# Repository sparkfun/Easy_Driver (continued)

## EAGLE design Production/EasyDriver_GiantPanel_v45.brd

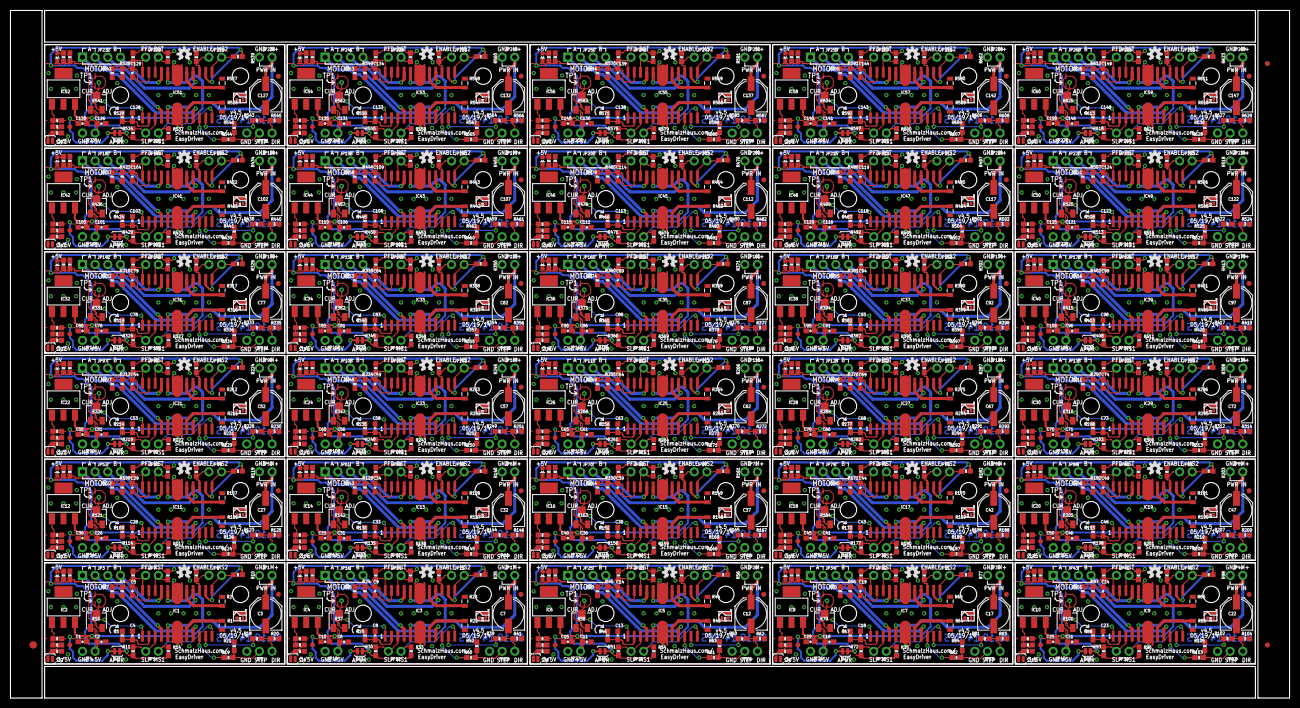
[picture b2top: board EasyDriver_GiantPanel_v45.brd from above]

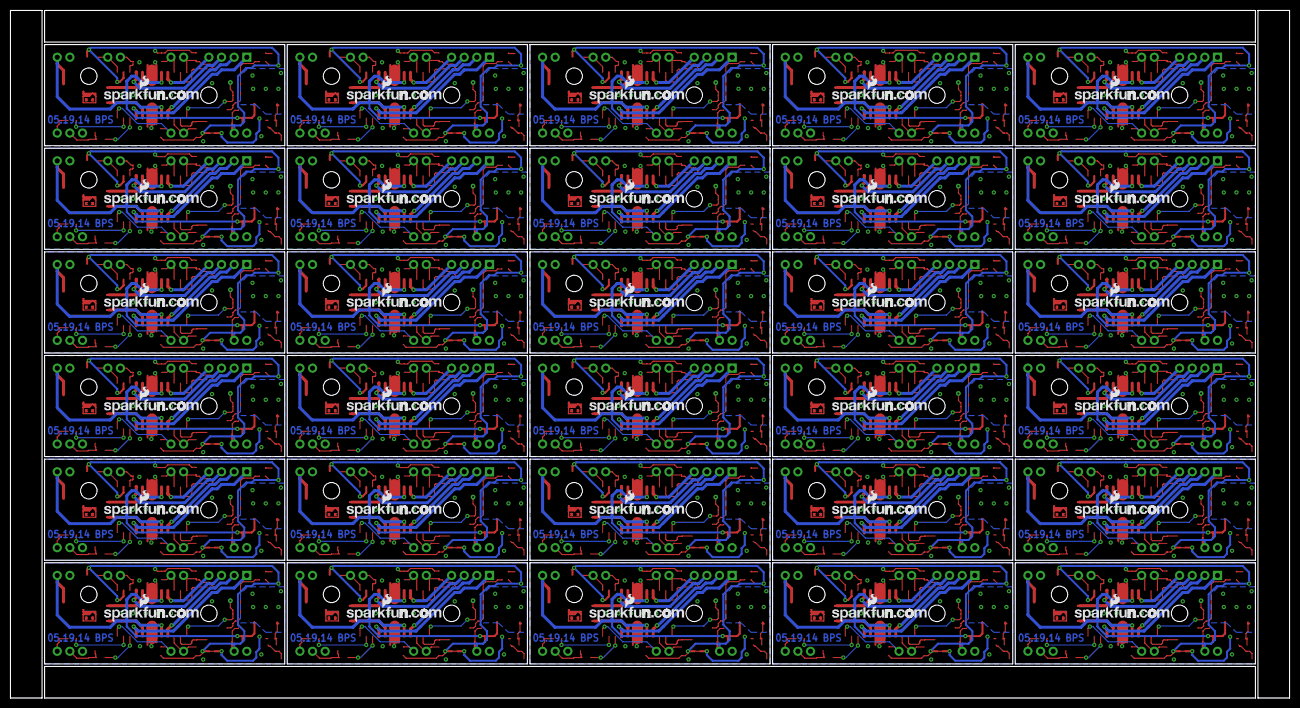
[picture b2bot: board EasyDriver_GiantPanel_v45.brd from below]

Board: 2 copper layers, 257.0 x 138.2 mm, 1383 parts (30 on the bottom side), 810 nets.

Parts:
C1, C10, C15, C20, C25, C30, C35, C40, C45, C50, C55, C60, C65, C70, C75, C80, C85, C90, C95, C100, C105, C110, C115, C120, C125, C130, C135, C140, C145, C150: .1uF; 0603-CAP
C2, C6, C11, C16, C21, C26, C31, C36, C41, C46, C51, C56, C61, C66, C71, C76, C81, C86, C91, C96, C101, C106, C111, C116, C121, C126, C131, C136, C141, C146: 1uf; 0603-CAP
C3, C7, C12, C17, C22, C27, C32, C37, C42, C47, C52, C57, C62, C67, C72, C77, C82, C87, C92, C97, C102, C107, C112, C117, C122, C127, C132, C137, C142, C147: 47uF; PANASONIC_D
C4, C5, C8, C9, C13, C14, C18, C19, C23, C24, C28, C29, C33, C34, C38, C39, C43, C44, C48, C49, C53, C54, C58, C59, C63, C64, C68, C69, C73, C74, C78, C79, C83, C84, C88, C89, C93, C94, C98, C99, C103, C104, C108, C109, C113, C114, C118, C119, C123, C124, C128, C129, C133, C134, C138, C139, C143, C144, C148, C149: 680pF; 0603-CAP
E$1: FIDUCIAL-1.5X3
E$4, E$6: FIDUCIAL-1X2
FID1, FID2, FID3, FID4, FID5, FID6, FID7, FID8, FID9, FID10, FID11, FID12, FID13, FID14, FID15, FID16, FID17, FID18, FID19, FID20, FID21, FID22, FID23, FID24, FID25, FID26, FID27, FID28, FID29, FID30, FID31, FID32, FID33, FID34, FID35, FID36, FID37, FID38, FID39, FID40, FID41, FID42, FID43, FID44, FID45, FID46, FID47, FID48, FID49, FID50, FID51, FID52, FID53, FID54, FID55, FID56, FID57, FID58, FID59, FID60: FIDUCIAL1X2; FIDUCIAL-1X2
IC1, IC3, IC5, IC7, IC9, IC11, IC13, IC15, IC17, IC19, IC21, IC23, IC25, IC27, IC29, IC31, IC33, IC35, IC37, IC39, IC41, IC43, IC45, IC47, IC49, IC51, IC53, IC55, IC57, IC59: A3967SLB; SO24W
IC2, IC4, IC6, IC8, IC10, IC12, IC14, IC16, IC18, IC20, IC22, IC24, IC26, IC28, IC30, IC32, IC34, IC36, IC38, IC40, IC42, IC44, IC46, IC48, IC50, IC52, IC54, IC56, IC58, IC60: V_REG_317SMD; SOT223
JP1, JP4, JP5, JP6, JP7, JP12, JP13, JP14, JP17, JP18, JP21, JP22, JP23, JP26, JP27, JP30, JP31, JP32, JP35, JP36, JP39, JP40, JP41, JP44, JP45, JP48, JP49, JP50, JP53, JP54, JP57, JP58, JP59, JP62, JP63, JP66, JP67, JP68, JP71, JP72, JP75, JP76, JP77, JP80, JP81, JP84, JP85, JP86, JP89, JP90, JP93, JP94, JP95, JP98, JP99, JP102, JP103, JP104, JP107, JP108, JP111, JP112, JP113, JP116, JP117, JP120, JP121, JP122, JP125, JP126, JP129, JP130, JP131, JP134, JP135, JP138, JP139, JP140, JP143, JP144, JP147, JP148, JP149, JP152, JP153, JP156, JP157, JP158, JP161, JP162, JP165, JP166, JP167, JP170, JP171, JP174, JP175, JP176, JP179, JP180, JP183, JP184, JP185, JP188, JP189, JP192, JP193, JP194, JP197, JP198, JP201, JP202, JP203, JP206, JP207, JP210, JP211, JP212, JP215, JP216, JP219, JP220, JP221, JP224, JP225, JP228, JP229, JP230, JP233, JP234, JP237, JP238, JP239, JP242, JP243, JP246, JP247, JP248, JP251, JP252, JP255, JP256, JP257, JP260, JP261, JP264, JP265, JP266, JP269, JP270: 1X02_NO_SILK
JP2, JP15, JP24, JP33, JP42, JP51, JP60, JP69, JP78, JP87, JP96, JP105, JP114, JP123, JP132, JP141, JP150, JP159, JP168, JP177, JP186, JP195, JP204, JP213, JP222, JP231, JP240, JP249, JP258, JP267: 1X03_NO_SILK
JP3, JP16, JP25, JP34, JP43, JP52, JP61, JP70, JP79, JP88, JP97, JP106, JP115, JP124, JP133, JP142, JP151, JP160, JP169, JP178, JP187, JP196, JP205, JP214, JP223, JP232, JP241, JP250, JP259, JP268: 1X04_NO_SILK
JP8, JP9, JP10, JP11, JP19, JP20, JP28, JP29, JP37, JP38, JP46, JP47, JP55, JP56, JP64, JP65, JP73, JP74, JP82, JP83, JP91, JP92, JP100, JP101, JP109, JP110, JP118, JP119, JP127, JP128, JP136, JP137, JP145, JP146, JP154, JP155, JP163, JP164, JP172, JP173, JP181, JP182, JP190, JP191, JP199, JP200, JP208, JP209, JP217, JP218, JP226, JP227, JP235, JP236, JP244, JP245, JP253, JP254, JP262, JP263: STAND-OFF
LOGO1, LOGO2, LOGO3, LOGO4, LOGO5, LOGO6, LOGO7, LOGO8, LOGO9, LOGO10, LOGO11, LOGO12, LOGO13, LOGO14, LOGO15, LOGO16, LOGO17, LOGO18, LOGO19, LOGO20, LOGO21, LOGO22, LOGO23, LOGO24, LOGO25, LOGO26, LOGO27, LOGO28, LOGO29, LOGO30: OSHW-LOGOS; OSHW-LOGO-S
PWR_LED, PWR_LED1, PWR_LED2, PWR_LED3, PWR_LED4, PWR_LED5, PWR_LED6, PWR_LED7, PWR_LED8, PWR_LED9, PWR_LED10, PWR_LED11, PWR_LED12, PWR_LED13, PWR_LED14, PWR_LED15, PWR_LED16, PWR_LED17, PWR_LED18, PWR_LED19, PWR_LED20, PWR_LED21, PWR_LED22, PWR_LED23, PWR_LED24, PWR_LED25, PWR_LED26, PWR_LED27, PWR_LED28, PWR_LED29: YELLOW; LED-0603
R1, R2, R22, R23, R43, R44, R64, R65, R85, R86, R106, R107, R127, R128, R148, R149, R169, R170, R190, R191, R211, R212, R232, R233, R253, R254, R274, R275, R295, R296, R316, R317, R337, R338, R358, R359, R379, R380, R400, R401, R421, R422, R442, R443, R463, R464, R484, R485, R505, R506, R526, R527, R547, R548, R568, R569, R589, R590, R610, R611: .75; 0805
R3, R4, R24, R25, R45, R46, R66, R67, R87, R88, R108, R109, R129, R130, R150, R151, R171, R172, R192, R193, R213, R214, R234, R235, R255, R256, R276, R277, R297, R298, R318, R319, R339, R340, R360, R361, R381, R382, R402, R403, R423, R424, R444, R445, R465, R466, R486, R487, R507, R508, R528, R529, R549, R550, R570, R571, R591, R592, R612, R613: 20K; 0603-RES
R5, R26, R47, R68, R89, R110, R131, R152, R173, R194, R215, R236, R257, R278, R299, R320, R341, R362, R383, R404, R425, R446, R467, R488, R509, R530, R551, R572, R593, R614: 2.49K; 0603-RES
R6, R27, R48, R69, R90, R111, R132, R153, R174, R195, R216, R237, R258, R279, R300, R321, R342, R363, R384, R405, R426, R447, R468, R489, R510, R531, R552, R573, R594, R615: 390; 0603-RES
R7, R36, R57, R78, R99, R120, R141, R162, R183, R204, R225, R246, R267, R288, R309, R330, R351, R372, R393, R414, R435, R456, R477, R498, R519, R540, R561, R582, R603, R624: 330; 0603-RES
R8, R28, R49, R70, R91, R112, R133, R154, R175, R196, R217, R238, R259, R280, R301, R322, R343, R364, R385, R406, R427, R448, R469, R490, R511, R532, R553, R574, R595, R616: 240; 0603-RES
R9, R18, R19, R29, R39, R40, R50, R60, R61, R71, R81, R82, R92, R102, R103, R113, R123, R124, R134, R144, R145, R155, R165, R166, R176, R186, R187, R197, R207, R208, R218, R228, R229, R239, R249, R250, R260, R270, R271, R281, R291, R292, R302, R312, R313, R323, R333, R334, R344, R354, R355, R365, R375, R376, R386, R396, R397, R407, R417, R418, R428, R438, R439, R449, R459, R460, R470, R480, R481, R491, R501, R502, R512, R522, R523, R533, R543, R544, R554, R564, R565, R575, R585, R586, R596, R606, R607, R617, R627, R628: 1K; 0603-RES
R10, R11, R12, R13, R14, R15, R20, R21, R30, R31, R32, R33, R34, R35, R41, R42, R51, R52, R53, R54, R55, R56, R62, R63, R72, R73, R74, R75, R76, R77, R83, R84, R93, R94, R95, R96, R97, R98, R104, R105, R114, R115, R116, R117, R118, R119, R125, R126, R135, R136, R137, R138, R139, R140, R146, R147, R156, R157, R158, R159, R160, R161, R167, R168, R177, R178, R179, R180, R181, R182, R188, R189, R198, R199, R200, R201, R202, R203, R209, R210, R219, R220, R221, R222, R223, R224, R230, R231, R240, R241, R242, R243, R244, R245, R251, R252, R261, R262, R263, R264, R265, R266, R272, R273, R282, R283, R284, R285, R286, R287, R293, R294, R303, R304, R305, R306, R307, R308, R314, R315, R324, R325, R326, R327, R328, R329, R335, R336, R345, R346, R347, R348, R349, R350, R356, R357, R366, R367, R368, R369, R370, R371, R377, R378, R387, R388, R389, R390, R391, R392, R398, R399, R408, R409, R410, R411, R412, R413, R419, R420, R429, R430, R431, R432, R433, R434, R440, R441, R450, R451, R452, R453, R454, R455, R461, R462, R471, R472, R473, R474, R475, R476, R482, R483, R492, R493, R494, R495, R496, R497, R503, R504, R513, R514, R515, R516, R517, R518, R524, R525, R534, R535, R536, R537, R538, R539, R545, R546, R555, R556, R557, R558, R559, R560, R566, R567, R576, R577, R578, R579, R580, R581, R587, R588, R597, R598, R599, R600, R601, R602, R608, R609, R618, R619, R620, R621, R622, R623, R629, R630: 10K; 0603-RES
R16, R37, R58, R79, R100, R121, R142, R163, R184, R205, R226, R247, R268, R289, R310, R331, R352, R373, R394, R415, R436, R457, R478, R499, R520, R541, R562, R583, R604, R625: 10K; TRIMPOT-3MM-2
R17, R38, R59, R80, R101, R122, R143, R164, R185, R206, R227, R248, R269, R290, R311, R332, R353, R374, R395, R416, R437, R458, R479, R500, R521, R542, R563, R584, R605, R626: 6.8K; 0603-RES
SJ1, SJ3, SJ5, SJ7, SJ9, SJ11, SJ13, SJ15, SJ17, SJ19, SJ21, SJ23, SJ25, SJ27, SJ29, SJ31, SJ33, SJ35, SJ37, SJ39, SJ41, SJ43, SJ45, SJ47, SJ49, SJ51, SJ53, SJ55, SJ57, SJ59: SOLDERJUMPERTRACE; SJ_2S-TRACE
SJ2, SJ4, SJ6, SJ8, SJ10, SJ12, SJ14, SJ16, SJ18, SJ20, SJ22, SJ24, SJ26, SJ28, SJ30, SJ32, SJ34, SJ36, SJ38, SJ40, SJ42, SJ44, SJ46, SJ48, SJ50, SJ52, SJ54, SJ56, SJ58, SJ60: SOLDERJUMPERNO; SJ_2S-NO
TP1, TP2, TP3, TP4, TP5, TP6, TP7, TP8, TP9, TP10, TP11, TP12, TP13, TP14, TP15, TP16, TP17, TP18, TP19, TP20, TP21, TP22, TP23, TP24, TP25, TP26, TP27, TP28, TP29, TP30: TEST-POINTTP_15TH_THRU; TP_15TH
U$1, U$3, U$5, U$7, U$9, U$11, U$13, U$15, U$17, U$19, U$21, U$23, U$25, U$27, U$29, U$31, U$33, U$35, U$37, U$39, U$41, U$43, U$45, U$47, U$49, U$51, U$53, U$55, U$57, U$59: SCHMALZHAUS_SMALL
U$2, U$4, U$6, U$8, U$10, U$12, U$14, U$16, U$18, U$20, U$22, U$24, U$26, U$28, U$30, U$32, U$34, U$36, U$38, U$40, U$42, U$44, U$46, U$48, U$50, U$52, U$54, U$56, U$58, U$60: LOGO-SFENEW; SFE-NEW-WEBLOGO

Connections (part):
5V_ALT: IC2.2, IC2.4, R8.2, SJ1.1
5V_ALT1: IC4.2, IC4.4, R28.2, SJ3.1
5V_ALT2: IC6.2, IC6.4, R49.2, SJ5.1
5V_ALT3: IC8.2, IC8.4, R70.2, SJ7.1
5V_ALT4: IC10.2, IC10.4, R91.2, SJ9.1
5V_ALT5: IC12.2, IC12.4, R112.2, SJ11.1
5V_ALT6: IC14.2, IC14.4, R133.2, SJ13.1
5V_ALT7: IC16.2, IC16.4, R154.2, SJ15.1
5V_ALT8: IC18.2, IC18.4, R175.2, SJ17.1
5V_ALT9: IC20.2, IC20.4, R196.2, SJ19.1
5V_ALT10: IC22.2, IC22.4, R217.2, SJ21.1
5V_ALT11: IC24.2, IC24.4, R238.2, SJ23.1
5V_ALT12: IC26.2, IC26.4, R259.2, SJ25.1
5V_ALT13: IC28.2, IC28.4, R280.2, SJ27.1
5V_ALT14: IC30.2, IC30.4, R301.2, SJ29.1
5V_ALT15: IC32.2, IC32.4, R322.2, SJ31.1
5V_ALT16: IC34.2, IC34.4, R343.2, SJ33.1
5V_ALT17: IC36.2, IC36.4, R364.2, SJ35.1
5V_ALT18: IC38.2, IC38.4, R385.2, SJ37.1
5V_ALT19: IC40.2, IC40.4, R406.2, SJ39.1
5V_ALT20: IC42.2, IC42.4, R427.2, SJ41.1
5V_ALT21: IC44.2, IC44.4, R448.2, SJ43.1
5V_ALT22: IC46.2, IC46.4, R469.2, SJ45.1
5V_ALT23: IC48.2, IC48.4, R490.2, SJ47.1
5V_ALT24: IC50.2, IC50.4, R511.2, SJ49.1
5V_ALT25: IC52.2, IC52.4, R532.2, SJ51.1
5V_ALT26: IC54.2, IC54.4, R553.2, SJ53.1
5V_ALT27: IC56.2, IC56.4, R574.2, SJ55.1
5V_ALT28: IC58.2, IC58.4, R595.2, SJ57.1
5V_ALT29: IC60.2, IC60.4, R616.2, SJ59.1
DIR: IC1.11, R18.1
DIR1: IC3.11, R39.1
DIR2: IC5.11, R60.1
DIR3: IC7.11, R81.1
DIR4: IC9.11, R102.1
DIR5: IC11.11, R123.1
DIR6: IC13.11, R144.1
DIR7: IC15.11, R165.1
DIR8: IC17.11, R186.1
DIR9: IC19.11, R207.1
DIR10: IC21.11, R228.1
DIR11: IC23.11, R249.1
DIR12: IC25.11, R270.1
DIR13: IC27.11, R291.1
DIR14: IC29.11, R312.1
DIR15: IC31.11, R333.1
DIR16: IC33.11, R354.1
DIR17: IC35.11, R375.1
DIR18: IC37.11, R396.1
DIR19: IC39.11, R417.1
DIR20: IC41.11, R438.1
DIR21: IC43.11, R459.1
DIR22: IC45.11, R480.1
DIR23: IC47.11, R501.1
DIR24: IC49.11, R522.1
DIR25: IC51.11, R543.1
DIR26: IC53.11, R564.1
DIR27: IC55.11, R585.1
DIR28: IC57.11, R606.1
DIR29: IC59.11, R627.1
DIR_IN: JP2.3, R18.2, R20.2
DIR_IN1: JP15.3, R39.2, R41.2
DIR_IN2: JP24.3, R60.2, R62.2
DIR_IN3: JP33.3, R81.2, R83.2
DIR_IN4: JP42.3, R102.2, R104.2
DIR_IN5: JP51.3, R123.2, R125.2
DIR_IN6: JP60.3, R144.2, R146.2
DIR_IN7: JP69.3, R165.2, R167.2
DIR_IN8: JP78.3, R186.2, R188.2
DIR_IN9: JP87.3, R207.2, R209.2
DIR_IN10: JP96.3, R228.2, R230.2
DIR_IN11: JP105.3, R249.2, R251.2
DIR_IN12: JP114.3, R270.2, R272.2
DIR_IN13: JP123.3, R291.2, R293.2
DIR_IN14: JP132.3, R312.2, R314.2
DIR_IN15: JP141.3, R333.2, R335.2
DIR_IN16: JP150.3, R354.2, R356.2
DIR_IN17: JP159.3, R375.2, R377.2
DIR_IN18: JP168.3, R396.2, R398.2
DIR_IN19: JP177.3, R417.2, R419.2
DIR_IN20: JP186.3, R438.2, R440.2
DIR_IN21: JP195.3, R459.2, R461.2
DIR_IN22: JP204.3, R480.2, R482.2
DIR_IN23: JP213.3, R501.2, R503.2
DIR_IN24: JP222.3, R522.2, R524.2
DIR_IN25: JP231.3, R543.2, R545.2
DIR_IN26: JP240.3, R564.2, R566.2
DIR_IN27: JP249.3, R585.2, R587.2
DIR_IN28: JP258.3, R606.2, R608.2
DIR_IN29: JP267.3, R627.2, R629.2
ENABLE: IC1.15, JP6.1, R13.2
ENABLE1: IC3.15, JP13.1, R32.2
ENABLE2: IC5.15, JP22.1, R53.2
ENABLE3: IC7.15, JP31.1, R74.2
ENABLE4: IC9.15, JP40.1, R95.2
ENABLE5: IC11.15, JP49.1, R116.2
ENABLE6: IC13.15, JP58.1, R137.2
ENABLE7: IC15.15, JP67.1, R158.2
ENABLE8: IC17.15, JP76.1, R179.2
ENABLE9: IC19.15, JP85.1, R200.2
ENABLE10: IC21.15, JP94.1, R221.2
ENABLE11: IC23.15, JP103.1, R242.2
ENABLE12: IC25.15, JP112.1, R263.2
ENABLE13: IC27.15, JP121.1, R284.2
ENABLE14: IC29.15, JP130.1, R305.2
ENABLE15: IC31.15, JP139.1, R326.2
ENABLE16: IC33.15, JP148.1, R347.2
ENABLE17: IC35.15, JP157.1, R368.2
ENABLE18: IC37.15, JP166.1, R389.2
ENABLE19: IC39.15, JP175.1, R410.2
ENABLE20: IC41.15, JP184.1, R431.2
ENABLE21: IC43.15, JP193.1, R452.2
ENABLE22: IC45.15, JP202.1, R473.2
ENABLE23: IC47.15, JP211.1, R494.2
ENABLE24: IC49.15, JP220.1, R515.2
ENABLE25: IC51.15, JP229.1, R536.2
ENABLE26: IC53.15, JP238.1, R557.2
ENABLE27: IC55.15, JP247.1, R578.2
ENABLE28: IC57.15, JP256.1, R599.2
ENABLE29: IC59.15, JP265.1, R620.2
GND: C1.2, C2.2, C3.-, C4.2, C5.2, IC1.6, IC1.7, IC1.18, IC1.19, JP1.1, JP2.1, JP4.2, PWR_LED.C, R1.1, R2.1, R3.1, R4.1, R5.1, R7.1, R13.1, R17.1, R20.1, R21.1, SJ2.2
GND1: C6.2, C7.-, C8.2, C9.2, C10.2, IC3.6, IC3.7, IC3.18, IC3.19, JP15.1, JP17.1, JP18.2, PWR_LED1.C, R22.1, R23.1, R24.1, R25.1, R26.1, R32.1, R36.1, R38.1, R41.1, R42.1, SJ4.2
GND2: C11.2, C12.-, C13.2, C14.2, C15.2, IC5.6, IC5.7, IC5.18, IC5.19, JP24.1, JP26.1, JP27.2, PWR_LED2.C, R43.1, R44.1, R45.1, R46.1, R47.1, R53.1, R57.1, R59.1, R62.1, R63.1, SJ6.2
GND3: C16.2, C17.-, C18.2, C19.2, C20.2, IC7.6, IC7.7, IC7.18, IC7.19, JP33.1, JP35.1, JP36.2, PWR_LED3.C, R64.1, R65.1, R66.1, R67.1, R68.1, R74.1, R78.1, R80.1, R83.1, R84.1, SJ8.2
GND4: C21.2, C22.-, C23.2, C24.2, C25.2, IC9.6, IC9.7, IC9.18, IC9.19, JP42.1, JP44.1, JP45.2, PWR_LED4.C, R85.1, R86.1, R87.1, R88.1, R89.1, R95.1, R99.1, R101.1, R104.1, R105.1, SJ10.2
GND5: C26.2, C27.-, C28.2, C29.2, C30.2, IC11.6, IC11.7, IC11.18, IC11.19, JP51.1, JP53.1, JP54.2, PWR_LED5.C, R106.1, R107.1, R108.1, R109.1, R110.1, R116.1, R120.1, R122.1, R125.1, R126.1, SJ12.2
GND6: C31.2, C32.-, C33.2, C34.2, C35.2, IC13.6, IC13.7, IC13.18, IC13.19, JP60.1, JP62.1, JP63.2, PWR_LED6.C, R127.1, R128.1, R129.1, R130.1, R131.1, R137.1, R141.1, R143.1, R146.1, R147.1, SJ14.2
GND7: C36.2, C37.-, C38.2, C39.2, C40.2, IC15.6, IC15.7, IC15.18, IC15.19, JP69.1, JP71.1, JP72.2, PWR_LED7.C, R148.1, R149.1, R150.1, R151.1, R152.1, R158.1, R162.1, R164.1, R167.1, R168.1, SJ16.2
GND8: C41.2, C42.-, C43.2, C44.2, C45.2, IC17.6, IC17.7, IC17.18, IC17.19, JP78.1, JP80.1, JP81.2, PWR_LED8.C, R169.1, R170.1, R171.1, R172.1, R173.1, R179.1, R183.1, R185.1, R188.1, R189.1, SJ18.2
GND9: C46.2, C47.-, C48.2, C49.2, C50.2, IC19.6, IC19.7, IC19.18, IC19.19, JP87.1, JP89.1, JP90.2, PWR_LED9.C, R190.1, R191.1, R192.1, R193.1, R194.1, R200.1, R204.1, R206.1, R209.1, R210.1, SJ20.2
GND10: C51.2, C52.-, C53.2, C54.2, C55.2, IC21.6, IC21.7, IC21.18, IC21.19, JP96.1, JP98.1, JP99.2, PWR_LED10.C, R211.1, R212.1, R213.1, R214.1, R215.1, R221.1, R225.1, R227.1, R230.1, R231.1, SJ22.2
GND11: C56.2, C57.-, C58.2, C59.2, C60.2, IC23.6, IC23.7, IC23.18, IC23.19, JP105.1, JP107.1, JP108.2, PWR_LED11.C, R232.1, R233.1, R234.1, R235.1, R236.1, R242.1, R246.1, R248.1, R251.1, R252.1, SJ24.2
GND12: C61.2, C62.-, C63.2, C64.2, C65.2, IC25.6, IC25.7, IC25.18, IC25.19, JP114.1, JP116.1, JP117.2, PWR_LED12.C, R253.1, R254.1, R255.1, R256.1, R257.1, R263.1, R267.1, R269.1, R272.1, R273.1, SJ26.2
GND13: C66.2, C67.-, C68.2, C69.2, C70.2, IC27.6, IC27.7, IC27.18, IC27.19, JP123.1, JP125.1, JP126.2, PWR_LED13.C, R274.1, R275.1, R276.1, R277.1, R278.1, R284.1, R288.1, R290.1, R293.1, R294.1, SJ28.2
GND14: C71.2, C72.-, C73.2, C74.2, C75.2, IC29.6, IC29.7, IC29.18, IC29.19, JP132.1, JP134.1, JP135.2, PWR_LED14.C, R295.1, R296.1, R297.1, R298.1, R299.1, R305.1, R309.1, R311.1, R314.1, R315.1, SJ30.2
GND15: C76.2, C77.-, C78.2, C79.2, C80.2, IC31.6, IC31.7, IC31.18, IC31.19, JP141.1, JP143.1, JP144.2, PWR_LED15.C, R316.1, R317.1, R318.1, R319.1, R320.1, R326.1, R330.1, R332.1, R335.1, R336.1, SJ32.2
GND16: C81.2, C82.-, C83.2, C84.2, C85.2, IC33.6, IC33.7, IC33.18, IC33.19, JP150.1, JP152.1, JP153.2, PWR_LED16.C, R337.1, R338.1, R339.1, R340.1, R341.1, R347.1, R351.1, R353.1, R356.1, R357.1, SJ34.2
GND17: C86.2, C87.-, C88.2, C89.2, C90.2, IC35.6, IC35.7, IC35.18, IC35.19, JP159.1, JP161.1, JP162.2, PWR_LED17.C, R358.1, R359.1, R360.1, R361.1, R362.1, R368.1, R372.1, R374.1, R377.1, R378.1, SJ36.2
GND18: C91.2, C92.-, C93.2, C94.2, C95.2, IC37.6, IC37.7, IC37.18, IC37.19, JP168.1, JP170.1, JP171.2, PWR_LED18.C, R379.1, R380.1, R381.1, R382.1, R383.1, R389.1, R393.1, R395.1, R398.1, R399.1, SJ38.2
GND19: C96.2, C97.-, C98.2, C99.2, C100.2, IC39.6, IC39.7, IC39.18, IC39.19, JP177.1, JP179.1, JP180.2, PWR_LED19.C, R400.1, R401.1, R402.1, R403.1, R404.1, R410.1, R414.1, R416.1, R419.1, R420.1, SJ40.2
GND20: C101.2, C102.-, C103.2, C104.2, C105.2, IC41.6, IC41.7, IC41.18, IC41.19, JP186.1, JP188.1, JP189.2, PWR_LED20.C, R421.1, R422.1, R423.1, R424.1, R425.1, R431.1, R435.1, R437.1, R440.1, R441.1, SJ42.2
GND21: C106.2, C107.-, C108.2, C109.2, C110.2, IC43.6, IC43.7, IC43.18, IC43.19, JP195.1, JP197.1, JP198.2, PWR_LED21.C, R442.1, R443.1, R444.1, R445.1, R446.1, R452.1, R456.1, R458.1, R461.1, R462.1, SJ44.2
GND22: C111.2, C112.-, C113.2, C114.2, C115.2, IC45.6, IC45.7, IC45.18, IC45.19, JP204.1, JP206.1, JP207.2, PWR_LED22.C, R463.1, R464.1, R465.1, R466.1, R467.1, R473.1, R477.1, R479.1, R482.1, R483.1, SJ46.2
GND23: C116.2, C117.-, C118.2, C119.2, C120.2, IC47.6, IC47.7, IC47.18, IC47.19, JP213.1, JP215.1, JP216.2, PWR_LED23.C, R484.1, R485.1, R486.1, R487.1, R488.1, R494.1, R498.1, R500.1, R503.1, R504.1, SJ48.2
GND24: C121.2, C122.-, C123.2, C124.2, C125.2, IC49.6, IC49.7, IC49.18, IC49.19, JP222.1, JP224.1, JP225.2, PWR_LED24.C, R505.1, R506.1, R507.1, R508.1, R509.1, R515.1, R519.1, R521.1, R524.1, R525.1, SJ50.2
GND25: C126.2, C127.-, C128.2, C129.2, C130.2, IC51.6, IC51.7, IC51.18, IC51.19, JP231.1, JP233.1, JP234.2, PWR_LED25.C, R526.1, R527.1, R528.1, R529.1, R530.1, R536.1, R540.1, R542.1, R545.1, R546.1, SJ52.2
GND26: C131.2, C132.-, C133.2, C134.2, C135.2, IC53.6, IC53.7, IC53.18, IC53.19, JP240.1, JP242.1, JP243.2, PWR_LED26.C, R547.1, R548.1, R549.1, R550.1, R551.1, R557.1, R561.1, R563.1, R566.1, R567.1, SJ54.2
GND27: C136.2, C137.-, C138.2, C139.2, C140.2, IC55.6, IC55.7, IC55.18, IC55.19, JP249.1, JP251.1, JP252.2, PWR_LED27.C, R568.1, R569.1, R570.1, R571.1, R572.1, R578.1, R582.1, R584.1, R587.1, R588.1, SJ56.2
GND28: C141.2, C142.-, C143.2, C144.2, C145.2, IC57.6, IC57.7, IC57.18, IC57.19, JP258.1, JP260.1, JP261.2, PWR_LED28.C, R589.1, R590.1, R591.1, R592.1, R593.1, R599.1, R603.1, R605.1, R608.1, R609.1, SJ58.2
GND29: C146.2, C147.-, C148.2, C149.2, C150.2, IC59.6, IC59.7, IC59.18, IC59.19, JP267.1, JP269.1, JP270.2, PWR_LED29.C, R610.1, R611.1, R612.1, R613.1, R614.1, R620.1, R624.1, R626.1, R629.1, R630.1, SJ60.2
MS1: IC1.12, JP5.1, R14.1
MS2: IC1.13, JP6.2, R10.1
MS3: IC3.12, JP12.1, R33.1
MS4: IC3.13, JP13.2, R35.1
MS5: IC5.12, JP21.1, R54.1
MS6: IC5.13, JP22.2, R56.1
MS7: IC7.12, JP30.1, R75.1
MS8: IC7.13, JP31.2, R77.1
MS9: IC9.12, JP39.1, R96.1
MS10: IC9.13, JP40.2, R98.1
MS11: IC11.12, JP48.1, R117.1
MS12: IC11.13, JP49.2, R119.1
MS13: IC13.12, JP57.1, R138.1
MS14: IC13.13, JP58.2, R140.1
MS15: IC15.12, JP66.1, R159.1
MS16: IC15.13, JP67.2, R161.1
MS17: IC17.12, JP75.1, R180.1
MS18: IC17.13, JP76.2, R182.1
MS19: IC19.12, JP84.1, R201.1
MS20: IC19.13, JP85.2, R203.1
MS21: IC21.12, JP93.1, R222.1
MS22: IC21.13, JP94.2, R224.1
MS23: IC23.12, JP102.1, R243.1
MS24: IC23.13, JP103.2, R245.1
MS25: IC25.12, JP111.1, R264.1
MS26: IC25.13, JP112.2, R266.1
MS27: IC27.12, JP120.1, R285.1
MS28: IC27.13, JP121.2, R287.1
MS29: IC29.12, JP129.1, R306.1
MS30: IC29.13, JP130.2, R308.1
MS31: IC31.12, JP138.1, R327.1
MS32: IC31.13, JP139.2, R329.1
MS33: IC33.12, JP147.1, R348.1
MS34: IC33.13, JP148.2, R350.1
MS35: IC35.12, JP156.1, R369.1
MS36: IC35.13, JP157.2, R371.1
MS37: IC37.12, JP165.1, R390.1
MS38: IC37.13, JP166.2, R392.1
MS39: IC39.12, JP174.1, R411.1
MS40: IC39.13, JP175.2, R413.1
MS41: IC41.12, JP183.1, R432.1
MS42: IC41.13, JP184.2, R434.1
MS43: IC43.12, JP192.1, R453.1
MS44: IC43.13, JP193.2, R455.1
MS45: IC45.12, JP201.1, R474.1
MS46: IC45.13, JP202.2, R476.1
MS47: IC47.12, JP210.1, R495.1
MS48: IC47.13, JP211.2, R497.1
MS49: IC49.12, JP219.1, R516.1
MS50: IC49.13, JP220.2, R518.1
MS51: IC51.12, JP228.1, R537.1
MS52: IC51.13, JP229.2, R539.1
MS53: IC53.12, JP237.1, R558.1
MS54: IC53.13, JP238.2, R560.1
MS55: IC55.12, JP246.1, R579.1
MS56: IC55.13, JP247.2, R581.1
MS57: IC57.12, JP255.1, R600.1
MS58: IC57.13, JP256.2, R602.1
MS59: IC59.12, JP264.1, R621.1
MS60: IC59.13, JP265.2, R623.1
unnamed: IC1.8, R1.2
unnamed: PWR_LED.A, R9.1
unnamed: IC1.17, R2.2
unnamed: R6.1, R7.2, SJ2.1
unnamed: C4.1, IC1.2, R3.2
unnamed: IC2.1, R6.2, R8.1
unnamed: C5.1, IC1.23, R4.2
unnamed: IC3.8, R22.2
unnamed: C8.1, IC3.2, R25.2
unnamed: C9.1, IC3.23, R24.2
unnamed: R5.2, R16.3
unnamed: IC3.17, R23.2
unnamed: IC4.1, R27.2, R28.1
unnamed: R26.2, R37.3
unnamed: PWR_LED1.A, R29.1
unnamed: R27.1, R36.2, SJ4.1
unnamed: IC5.8, R43.2
unnamed: C13.1, IC5.2, R46.2
unnamed: C14.1, IC5.23, R45.2
unnamed: IC5.17, R44.2
unnamed: IC6.1, R48.2, R49.1
unnamed: R47.2, R58.3
unnamed: PWR_LED2.A, R50.1
unnamed: R48.1, R57.2, SJ6.1
unnamed: IC7.8, R64.2
unnamed: C18.1, IC7.2, R67.2
unnamed: C19.1, IC7.23, R66.2
unnamed: IC7.17, R65.2
unnamed: IC8.1, R69.2, R70.1
unnamed: R68.2, R79.3
unnamed: PWR_LED3.A, R71.1
unnamed: R69.1, R78.2, SJ8.1
unnamed: IC9.8, R85.2
unnamed: C23.1, IC9.2, R88.2
unnamed: C24.1, IC9.23, R87.2
unnamed: IC9.17, R86.2
unnamed: IC10.1, R90.2, R91.1
unnamed: R89.2, R100.3
unnamed: PWR_LED4.A, R92.1
unnamed: R90.1, R99.2, SJ10.1
unnamed: IC11.8, R106.2
unnamed: C28.1, IC11.2, R109.2
unnamed: C29.1, IC11.23, R108.2
unnamed: IC11.17, R107.2
unnamed: IC12.1, R111.2, R112.1
unnamed: R110.2, R121.3
unnamed: PWR_LED5.A, R113.1
unnamed: R111.1, R120.2, SJ12.1
unnamed: IC13.8, R127.2
unnamed: C33.1, IC13.2, R130.2
unnamed: C34.1, IC13.23, R129.2
unnamed: IC13.17, R128.2
unnamed: IC14.1, R132.2, R133.1
unnamed: R131.2, R142.3
unnamed: PWR_LED6.A, R134.1
unnamed: R132.1, R141.2, SJ14.1
unnamed: IC15.8, R148.2
unnamed: C38.1, IC15.2, R151.2
unnamed: C39.1, IC15.23, R150.2
unnamed: IC15.17, R149.2
unnamed: IC16.1, R153.2, R154.1
unnamed: R152.2, R163.3
unnamed: PWR_LED7.A, R155.1
unnamed: R153.1, R162.2, SJ16.1
unnamed: IC17.8, R169.2
unnamed: C43.1, IC17.2, R172.2
unnamed: C44.1, IC17.23, R171.2
unnamed: IC17.17, R170.2
unnamed: IC18.1, R174.2, R175.1
unnamed: R173.2, R184.3
unnamed: PWR_LED8.A, R176.1
unnamed: R174.1, R183.2, SJ18.1
unnamed: IC19.8, R190.2
unnamed: C48.1, IC19.2, R193.2
unnamed: C49.1, IC19.23, R192.2
unnamed: IC19.17, R191.2
unnamed: IC20.1, R195.2, R196.1
unnamed: R194.2, R205.3
unnamed: PWR_LED9.A, R197.1
unnamed: R195.1, R204.2, SJ20.1
unnamed: IC21.8, R211.2
unnamed: C53.1, IC21.2, R214.2
unnamed: C54.1, IC21.23, R213.2
unnamed: IC21.17, R212.2
unnamed: IC22.1, R216.2, R217.1
unnamed: R215.2, R226.3
unnamed: PWR_LED10.A, R218.1
unnamed: R216.1, R225.2, SJ22.1
unnamed: IC23.8, R232.2
unnamed: C58.1, IC23.2, R235.2
unnamed: C59.1, IC23.23, R234.2
unnamed: IC23.17, R233.2
unnamed: IC24.1, R237.2, R238.1
unnamed: R236.2, R247.3
unnamed: PWR_LED11.A, R239.1
unnamed: R237.1, R246.2, SJ24.1
unnamed: IC25.8, R253.2
unnamed: C63.1, IC25.2, R256.2
unnamed: C64.1, IC25.23, R255.2
unnamed: IC25.17, R254.2
unnamed: IC26.1, R258.2, R259.1
unnamed: R257.2, R268.3
unnamed: PWR_LED12.A, R260.1
unnamed: R258.1, R267.2, SJ26.1
unnamed: IC27.8, R274.2
unnamed: C68.1, IC27.2, R277.2
unnamed: C69.1, IC27.23, R276.2
unnamed: IC27.17, R275.2
unnamed: IC28.1, R279.2, R280.1
unnamed: R278.2, R289.3
unnamed: PWR_LED13.A, R281.1
unnamed: R279.1, R288.2, SJ28.1
unnamed: IC29.8, R295.2
unnamed: C73.1, IC29.2, R298.2
unnamed: C74.1, IC29.23, R297.2
unnamed: IC29.17, R296.2
unnamed: IC30.1, R300.2, R301.1
unnamed: R299.2, R310.3
unnamed: PWR_LED14.A, R302.1
unnamed: R300.1, R309.2, SJ30.1
unnamed: IC31.8, R316.2
unnamed: C78.1, IC31.2, R319.2
unnamed: C79.1, IC31.23, R318.2
unnamed: IC31.17, R317.2
unnamed: IC32.1, R321.2, R322.1
unnamed: R320.2, R331.3
unnamed: PWR_LED15.A, R323.1
unnamed: R321.1, R330.2, SJ32.1
unnamed: IC33.8, R337.2
unnamed: C83.1, IC33.2, R340.2
unnamed: C84.1, IC33.23, R339.2
unnamed: IC33.17, R338.2
unnamed: IC34.1, R342.2, R343.1
unnamed: R341.2, R352.3
unnamed: PWR_LED16.A, R344.1
unnamed: R342.1, R351.2, SJ34.1
unnamed: IC35.8, R358.2
unnamed: C88.1, IC35.2, R361.2
unnamed: C89.1, IC35.23, R360.2
unnamed: IC35.17, R359.2
unnamed: IC36.1, R363.2, R364.1
unnamed: R362.2, R373.3
unnamed: PWR_LED17.A, R365.1
unnamed: R363.1, R372.2, SJ36.1
unnamed: IC37.8, R379.2
unnamed: C93.1, IC37.2, R382.2
unnamed: C94.1, IC37.23, R381.2
unnamed: IC37.17, R380.2
unnamed: IC38.1, R384.2, R385.1
unnamed: R383.2, R394.3
unnamed: PWR_LED18.A, R386.1
unnamed: R384.1, R393.2, SJ38.1
unnamed: IC39.8, R400.2
unnamed: C98.1, IC39.2, R403.2
unnamed: C99.1, IC39.23, R402.2
unnamed: IC39.17, R401.2
unnamed: IC40.1, R405.2, R406.1
unnamed: R404.2, R415.3
unnamed: PWR_LED19.A, R407.1
unnamed: R405.1, R414.2, SJ40.1
unnamed: IC41.8, R421.2
unnamed: C103.1, IC41.2, R424.2
unnamed: C104.1, IC41.23, R423.2
unnamed: IC41.17, R422.2
unnamed: IC42.1, R426.2, R427.1
unnamed: R425.2, R436.3
unnamed: PWR_LED20.A, R428.1
unnamed: R426.1, R435.2, SJ42.1
unnamed: IC43.8, R442.2
unnamed: C108.1, IC43.2, R445.2
unnamed: C109.1, IC43.23, R444.2
unnamed: IC43.17, R443.2
unnamed: IC44.1, R447.2, R448.1
unnamed: R446.2, R457.3
unnamed: PWR_LED21.A, R449.1
unnamed: R447.1, R456.2, SJ44.1
unnamed: IC45.8, R463.2
unnamed: C113.1, IC45.2, R466.2
unnamed: C114.1, IC45.23, R465.2
unnamed: IC45.17, R464.2
unnamed: IC46.1, R468.2, R469.1
unnamed: R467.2, R478.3
unnamed: PWR_LED22.A, R470.1
unnamed: R468.1, R477.2, SJ46.1
unnamed: IC47.8, R484.2
unnamed: C118.1, IC47.2, R487.2
unnamed: C119.1, IC47.23, R486.2
unnamed: IC47.17, R485.2
unnamed: IC48.1, R489.2, R490.1
unnamed: R488.2, R499.3
unnamed: PWR_LED23.A, R491.1
unnamed: R489.1, R498.2, SJ48.1
unnamed: IC49.8, R505.2
unnamed: C123.1, IC49.2, R508.2
unnamed: C124.1, IC49.23, R507.2
unnamed: IC49.17, R506.2
unnamed: IC50.1, R510.2, R511.1
unnamed: R509.2, R520.3
unnamed: PWR_LED24.A, R512.1
unnamed: R510.1, R519.2, SJ50.1
unnamed: IC51.8, R526.2
unnamed: C128.1, IC51.2, R529.2
unnamed: C129.1, IC51.23, R528.2
unnamed: IC51.17, R527.2
unnamed: IC52.1, R531.2, R532.1
unnamed: R530.2, R541.3
unnamed: PWR_LED25.A, R533.1
unnamed: R531.1, R540.2, SJ52.1
unnamed: IC53.8, R547.2
unnamed: C133.1, IC53.2, R550.2
unnamed: C134.1, IC53.23, R549.2
unnamed: IC53.17, R548.2
unnamed: IC54.1, R552.2, R553.1
unnamed: R551.2, R562.3
unnamed: PWR_LED26.A, R554.1
unnamed: R552.1, R561.2, SJ54.1
unnamed: IC55.8, R568.2
unnamed: C138.1, IC55.2, R571.2
unnamed: C139.1, IC55.23, R570.2
unnamed: IC55.17, R569.2
unnamed: IC56.1, R573.2, R574.1
unnamed: R572.2, R583.3
unnamed: PWR_LED27.A, R575.1
unnamed: R573.1, R582.2, SJ56.1
unnamed: IC57.8, R589.2
unnamed: C143.1, IC57.2, R592.2
unnamed: C144.1, IC57.23, R591.2
unnamed: IC57.17, R590.2
unnamed: IC58.1, R594.2, R595.1
unnamed: R593.2, R604.3
unnamed: PWR_LED28.A, R596.1
unnamed: R594.1, R603.2, SJ58.1
unnamed: IC59.8, R610.2
unnamed: C148.1, IC59.2, R613.2
unnamed: C149.1, IC59.23, R612.2
unnamed: IC59.17, R611.2
unnamed: IC60.1, R615.2, R616.1
unnamed: R614.2, R625.3
unnamed: PWR_LED29.A, R617.1
unnamed: R615.1, R624.2, SJ60.1
OUT1A: IC1.16, JP3.3
OUT1A1: IC3.16, JP16.3
OUT1A2: IC5.16, JP25.3
OUT1A3: IC7.16, JP34.3
OUT1A4: IC9.16, JP43.3
OUT1A5: IC11.16, JP52.3
OUT1A6: IC13.16, JP61.3
OUT1A7: IC15.16, JP70.3
OUT1A8: IC17.16, JP79.3
OUT1A9: IC19.16, JP88.3
OUT1A10: IC21.16, JP97.3
OUT1A11: IC23.16, JP106.3
OUT1A12: IC25.16, JP115.3
OUT1A13: IC27.16, JP124.3
OUT1A14: IC29.16, JP133.3
OUT1A15: IC31.16, JP142.3
OUT1A16: IC33.16, JP151.3
OUT1A17: IC35.16, JP160.3
OUT1A18: IC37.16, JP169.3
OUT1A19: IC39.16, JP178.3
OUT1A20: IC41.16, JP187.3
OUT1A21: IC43.16, JP196.3
OUT1A22: IC45.16, JP205.3
OUT1A23: IC47.16, JP214.3
OUT1A24: IC49.16, JP223.3
OUT1A25: IC51.16, JP232.3
OUT1A26: IC53.16, JP241.3
OUT1A27: IC55.16, JP250.3
OUT1A28: IC57.16, JP259.3
OUT1A29: IC59.16, JP268.3
OUT1B: IC1.21, JP3.4
OUT1B1: IC3.21, JP16.4
OUT1B2: IC5.21, JP25.4
OUT1B3: IC7.21, JP34.4
OUT1B4: IC9.21, JP43.4
OUT1B5: IC11.21, JP52.4
OUT1B6: IC13.21, JP61.4
OUT1B7: IC15.21, JP70.4
OUT1B8: IC17.21, JP79.4
OUT1B9: IC19.21, JP88.4
OUT1B10: IC21.21, JP97.4
OUT1B11: IC23.21, JP106.4
OUT1B12: IC25.21, JP115.4
OUT1B13: IC27.21, JP124.4
OUT1B14: IC29.21, JP133.4
OUT1B15: IC31.21, JP142.4
OUT1B16: IC33.21, JP151.4
OUT1B17: IC35.21, JP160.4
OUT1B18: IC37.21, JP169.4
OUT1B19: IC39.21, JP178.4
OUT1B20: IC41.21, JP187.4
OUT1B21: IC43.21, JP196.4
OUT1B22: IC45.21, JP205.4
OUT1B23: IC47.21, JP214.4
OUT1B24: IC49.21, JP223.4
OUT1B25: IC51.21, JP232.4
OUT1B26: IC53.21, JP241.4
OUT1B27: IC55.21, JP250.4
OUT1B28: IC57.21, JP259.4
OUT1B29: IC59.21, JP268.4
OUT2A: IC1.9, JP3.1
OUT2A1: IC3.9, JP16.1
OUT2A2: IC5.9, JP25.1
OUT2A3: IC7.9, JP34.1
OUT2A4: IC9.9, JP43.1
OUT2A5: IC11.9, JP52.1
OUT2A6: IC13.9, JP61.1
OUT2A7: IC15.9, JP70.1
OUT2A8: IC17.9, JP79.1
OUT2A9: IC19.9, JP88.1
OUT2A10: IC21.9, JP97.1
OUT2A11: IC23.9, JP106.1
OUT2A12: IC25.9, JP115.1
OUT2A13: IC27.9, JP124.1
OUT2A14: IC29.9, JP133.1
OUT2A15: IC31.9, JP142.1
OUT2A16: IC33.9, JP151.1
OUT2A17: IC35.9, JP160.1
OUT2A18: IC37.9, JP169.1
OUT2A19: IC39.9, JP178.1
OUT2A20: IC41.9, JP187.1
OUT2A21: IC43.9, JP196.1
OUT2A22: IC45.9, JP205.1
OUT2A23: IC47.9, JP214.1
OUT2A24: IC49.9, JP223.1
OUT2A25: IC51.9, JP232.1
OUT2A26: IC53.9, JP241.1
OUT2A27: IC55.9, JP250.1
OUT2A28: IC57.9, JP259.1
OUT2A29: IC59.9, JP268.1
OUT2B: IC1.4, JP3.2
OUT2B1: IC3.4, JP16.2
OUT2B2: IC5.4, JP25.2
OUT2B3: IC7.4, JP34.2
OUT2B4: IC9.4, JP43.2
OUT2B5: IC11.4, JP52.2
OUT2B6: IC13.4, JP61.2
OUT2B7: IC15.4, JP70.2
OUT2B8: IC17.4, JP79.2
OUT2B9: IC19.4, JP88.2
OUT2B10: IC21.4, JP97.2
OUT2B11: IC23.4, JP106.2
OUT2B12: IC25.4, JP115.2
OUT2B13: IC27.4, JP124.2
OUT2B14: IC29.4, JP133.2
OUT2B15: IC31.4, JP142.2
OUT2B16: IC33.4, JP151.2
OUT2B17: IC35.4, JP160.2
OUT2B18: IC37.4, JP169.2
OUT2B19: IC39.4, JP178.2
OUT2B20: IC41.4, JP187.2
OUT2B21: IC43.4, JP196.2
OUT2B22: IC45.4, JP205.2
OUT2B23: IC47.4, JP214.2
OUT2B24: IC49.4, JP223.2
OUT2B25: IC51.4, JP232.2
OUT2B26: IC53.4, JP241.2
OUT2B27: IC55.4, JP250.2
OUT2B28: IC57.4, JP259.2
OUT2B29: IC59.4, JP268.2
PFD: IC1.24, JP7.1, R12.1, R17.2
PFD1: IC3.24, JP14.1, R31.1, R38.2
PFD2: IC5.24, JP23.1, R52.1, R59.2
PFD3: IC7.24, JP32.1, R73.1, R80.2
PFD4: IC9.24, JP41.1, R94.1, R101.2
PFD5: IC11.24, JP50.1, R115.1, R122.2
PFD6: IC13.24, JP59.1, R136.1, R143.2
PFD7: IC15.24, JP68.1, R157.1, R164.2
PFD8: IC17.24, JP77.1, R178.1, R185.2
PFD9: IC19.24, JP86.1, R199.1, R206.2
PFD10: IC21.24, JP95.1, R220.1, R227.2
PFD11: IC23.24, JP104.1, R241.1, R248.2
PFD12: IC25.24, JP113.1, R262.1, R269.2
PFD13: IC27.24, JP122.1, R283.1, R290.2
PFD14: IC29.24, JP131.1, R304.1, R311.2
PFD15: IC31.24, JP140.1, R325.1, R332.2
PFD16: IC33.24, JP149.1, R346.1, R353.2
PFD17: IC35.24, JP158.1, R367.1, R374.2
PFD18: IC37.24, JP167.1, R388.1, R395.2
PFD19: IC39.24, JP176.1, R409.1, R416.2
PFD20: IC41.24, JP185.1, R430.1, R437.2
PFD21: IC43.24, JP194.1, R451.1, R458.2
PFD22: IC45.24, JP203.1, R472.1, R479.2
PFD23: IC47.24, JP212.1, R493.1, R500.2
PFD24: IC49.24, JP221.1, R514.1, R521.2
PFD25: IC51.24, JP230.1, R535.1, R542.2
PFD26: IC53.24, JP239.1, R556.1, R563.2
PFD27: IC55.24, JP248.1, R577.1, R584.2
PFD28: IC57.24, JP257.1, R598.1, R605.2
PFD29: IC59.24, JP266.1, R619.1, R626.2
RESET: IC1.22, JP7.2, R15.1
RESET1: IC3.22, JP14.2, R34.1
RESET2: IC5.22, JP23.2, R55.1
RESET3: IC7.22, JP32.2, R76.1
RESET4: IC9.22, JP41.2, R97.1
RESET5: IC11.22, JP50.2, R118.1
RESET6: IC13.22, JP59.2, R139.1
RESET7: IC15.22, JP68.2, R160.1
RESET8: IC17.22, JP77.2, R181.1
RESET9: IC19.22, JP86.2, R202.1
RESET10: IC21.22, JP95.2, R223.1
RESET11: IC23.22, JP104.2, R244.1
RESET12: IC25.22, JP113.2, R265.1
RESET13: IC27.22, JP122.2, R286.1
RESET14: IC29.22, JP131.2, R307.1
RESET15: IC31.22, JP140.2, R328.1
RESET16: IC33.22, JP149.2, R349.1
RESET17: IC35.22, JP158.2, R370.1
RESET18: IC37.22, JP167.2, R391.1
RESET19: IC39.22, JP176.2, R412.1
RESET20: IC41.22, JP185.2, R433.1
RESET21: IC43.22, JP194.2, R454.1
RESET22: IC45.22, JP203.2, R475.1
RESET23: IC47.22, JP212.2, R496.1
RESET24: IC49.22, JP221.2, R517.1
RESET25: IC51.22, JP230.2, R538.1
RESET26: IC53.22, JP239.2, R559.1
RESET27: IC55.22, JP248.2, R580.1
RESET28: IC57.22, JP257.2, R601.1
RESET29: IC59.22, JP266.2, R622.1
SLEEP: IC1.3, JP5.2, R11.1
SLEEP1: IC3.3, JP12.2, R30.1
SLEEP2: IC5.3, JP21.2, R51.1
SLEEP3: IC7.3, JP30.2, R72.1
SLEEP4: IC9.3, JP39.2, R93.1
SLEEP5: IC11.3, JP48.2, R114.1
SLEEP6: IC13.3, JP57.2, R135.1
SLEEP7: IC15.3, JP66.2, R156.1
SLEEP8: IC17.3, JP75.2, R177.1
SLEEP9: IC19.3, JP84.2, R198.1
SLEEP10: IC21.3, JP93.2, R219.1
SLEEP11: IC23.3, JP102.2, R240.1
SLEEP12: IC25.3, JP111.2, R261.1
SLEEP13: IC27.3, JP120.2, R282.1
SLEEP14: IC29.3, JP129.2, R303.1
SLEEP15: IC31.3, JP138.2, R324.1
SLEEP16: IC33.3, JP147.2, R345.1
SLEEP17: IC35.3, JP156.2, R366.1
SLEEP18: IC37.3, JP165.2, R387.1
SLEEP19: IC39.3, JP174.2, R408.1
SLEEP20: IC41.3, JP183.2, R429.1
SLEEP21: IC43.3, JP192.2, R450.1
SLEEP22: IC45.3, JP201.2, R471.1
SLEEP23: IC47.3, JP210.2, R492.1
SLEEP24: IC49.3, JP219.2, R513.1
SLEEP25: IC51.3, JP228.2, R534.1
SLEEP26: IC53.3, JP237.2, R555.1
SLEEP27: IC55.3, JP246.2, R576.1
SLEEP28: IC57.3, JP255.2, R597.1
SLEEP29: IC59.3, JP264.2, R618.1
STEP: IC1.10, R19.1
STEP1: IC3.10, R40.1
STEP2: IC5.10, R61.1
STEP3: IC7.10, R82.1
STEP4: IC9.10, R103.1
STEP5: IC11.10, R124.1
STEP6: IC13.10, R145.1
STEP7: IC15.10, R166.1
STEP8: IC17.10, R187.1
STEP9: IC19.10, R208.1
STEP10: IC21.10, R229.1
STEP11: IC23.10, R250.1
STEP12: IC25.10, R271.1
STEP13: IC27.10, R292.1
STEP14: IC29.10, R313.1
STEP15: IC31.10, R334.1
STEP16: IC33.10, R355.1
STEP17: IC35.10, R376.1
STEP18: IC37.10, R397.1
STEP19: IC39.10, R418.1
STEP20: IC41.10, R439.1
STEP21: IC43.10, R460.1
STEP22: IC45.10, R481.1
STEP23: IC47.10, R502.1
STEP24: IC49.10, R523.1
STEP25: IC51.10, R544.1
STEP26: IC53.10, R565.1
STEP27: IC55.10, R586.1
STEP28: IC57.10, R607.1
STEP29: IC59.10, R628.1
STEP_IN: JP2.2, R19.2, R21.2
STEP_IN1: JP15.2, R40.2, R42.2
STEP_IN2: JP24.2, R61.2, R63.2
STEP_IN3: JP33.2, R82.2, R84.2
STEP_IN4: JP42.2, R103.2, R105.2
STEP_IN5: JP51.2, R124.2, R126.2
STEP_IN6: JP60.2, R145.2, R147.2
STEP_IN7: JP69.2, R166.2, R168.2
STEP_IN8: JP78.2, R187.2, R189.2
STEP_IN9: JP87.2, R208.2, R210.2
STEP_IN10: JP96.2, R229.2, R231.2
STEP_IN11: JP105.2, R250.2, R252.2
STEP_IN12: JP114.2, R271.2, R273.2
STEP_IN13: JP123.2, R292.2, R294.2
STEP_IN14: JP132.2, R313.2, R315.2
STEP_IN15: JP141.2, R334.2, R336.2
STEP_IN16: JP150.2, R355.2, R357.2
STEP_IN17: JP159.2, R376.2, R378.2
STEP_IN18: JP168.2, R397.2, R399.2
STEP_IN19: JP177.2, R418.2, R420.2
STEP_IN20: JP186.2, R439.2, R441.2
STEP_IN21: JP195.2, R460.2, R462.2
STEP_IN22: JP204.2, R481.2, R483.2
STEP_IN23: JP213.2, R502.2, R504.2
STEP_IN24: JP222.2, R523.2, R525.2
STEP_IN25: JP231.2, R544.2, R546.2
STEP_IN26: JP240.2, R565.2, R567.2
STEP_IN27: JP249.2, R586.2, R588.2
STEP_IN28: JP258.2, R607.2, R609.2
STEP_IN29: JP267.2, R628.2, R630.2
V+: C1.1, C3.+, IC1.5, IC1.20, IC2.3, JP1.2
V+1: C7.+, C10.1, IC3.5, IC3.20, IC4.3, JP17.2
V+2: C12.+, C15.1, IC5.5, IC5.20, IC6.3, JP26.2
V+3: C17.+, C20.1, IC7.5, IC7.20, IC8.3, JP35.2
V+4: C22.+, C25.1, IC9.5, IC9.20, IC10.3, JP44.2
V+5: C27.+, C30.1, IC11.5, IC11.20, IC12.3, JP53.2
V+6: C32.+, C35.1, IC13.5, IC13.20, IC14.3, JP62.2
V+7: C37.+, C40.1, IC15.5, IC15.20, IC16.3, JP71.2
V+8: C42.+, C45.1, IC17.5, IC17.20, IC18.3, JP80.2
V+9: C47.+, C50.1, IC19.5, IC19.20, IC20.3, JP89.2
V+10: C52.+, C55.1, IC21.5, IC21.20, IC22.3, JP98.2
V+11: C57.+, C60.1, IC23.5, IC23.20, IC24.3, JP107.2
V+12: C62.+, C65.1, IC25.5, IC25.20, IC26.3, JP116.2
V+13: C67.+, C70.1, IC27.5, IC27.20, IC28.3, JP125.2
V+14: C72.+, C75.1, IC29.5, IC29.20, IC30.3, JP134.2
V+15: C77.+, C80.1, IC31.5, IC31.20, IC32.3, JP143.2
V+16: C82.+, C85.1, IC33.5, IC33.20, IC34.3, JP152.2
V+17: C87.+, C90.1, IC35.5, IC35.20, IC36.3, JP161.2
V+18: C92.+, C95.1, IC37.5, IC37.20, IC38.3, JP170.2
V+19: C97.+, C100.1, IC39.5, IC39.20, IC40.3, JP179.2
V+20: C102.+, C105.1, IC41.5, IC41.20, IC42.3, JP188.2
V+21: C107.+, C110.1, IC43.5, IC43.20, IC44.3, JP197.2
V+22: C112.+, C115.1, IC45.5, IC45.20, IC46.3, JP206.2
V+23: C117.+, C120.1, IC47.5, IC47.20, IC48.3, JP215.2
V+24: C122.+, C125.1, IC49.5, IC49.20, IC50.3, JP224.2
V+25: C127.+, C130.1, IC51.5, IC51.20, IC52.3, JP233.2
V+26: C132.+, C135.1, IC53.5, IC53.20, IC54.3, JP242.2
V+27: C137.+, C140.1, IC55.5, IC55.20, IC56.3, JP251.2
V+28: C142.+, C145.1, IC57.5, IC57.20, IC58.3, JP260.2
V+29: C147.+, C150.1, IC59.5, IC59.20, IC60.3, JP269.2
VCC: C2.1, IC1.14, JP4.1, R9.2, R10.2, R11.2, R12.2, R14.2, R15.2, R16.1, SJ1.2
VCC1: C6.1, IC3.14, JP18.1, R29.2, R30.2, R31.2, R33.2, R34.2, R35.2, R37.1, SJ3.2
VCC2: C11.1, IC5.14, JP27.1, R50.2, R51.2, R52.2, R54.2, R55.2, R56.2, R58.1, SJ5.2
VCC3: C16.1, IC7.14, JP36.1, R71.2, R72.2, R73.2, R75.2, R76.2, R77.2, R79.1, SJ7.2
VCC4: C21.1, IC9.14, JP45.1, R92.2, R93.2, R94.2, R96.2, R97.2, R98.2, R100.1, SJ9.2
VCC5: C26.1, IC11.14, JP54.1, R113.2, R114.2, R115.2, R117.2, R118.2, R119.2, R121.1, SJ11.2
VCC6: C31.1, IC13.14, JP63.1, R134.2, R135.2, R136.2, R138.2, R139.2, R140.2, R142.1, SJ13.2
VCC7: C36.1, IC15.14, JP72.1, R155.2, R156.2, R157.2, R159.2, R160.2, R161.2, R163.1, SJ15.2
VCC8: C41.1, IC17.14, JP81.1, R176.2, R177.2, R178.2, R180.2, R181.2, R182.2, R184.1, SJ17.2
VCC9: C46.1, IC19.14, JP90.1, R197.2, R198.2, R199.2, R201.2, R202.2, R203.2, R205.1, SJ19.2
VCC10: C51.1, IC21.14, JP99.1, R218.2, R219.2, R220.2, R222.2, R223.2, R224.2, R226.1, SJ21.2
VCC11: C56.1, IC23.14, JP108.1, R239.2, R240.2, R241.2, R243.2, R244.2, R245.2, R247.1, SJ23.2
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
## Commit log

2014-03-19 Bringing design in from SchmalzHaus SVN to SparkFun GitHub. Also new version - 4.5 - with minor updates (footprints mainly, but also some extra protection resistors.)
2014-03-28 Version 4.5 updates -
    * All Rs and Cs are now normal 0603 SparkFun footprints
    * Added series Rs and pull downs for STEP and DIR inputs
    * Updated pot footprint to TRIMPOT-3MM-2 for better soldering
    * Switched license from CC BY 3.0 to CC BY-SA 3.0
    * Fixed pot direction silk screen
2014-04-01 Small updates to schematic and board
    * Rotated ground symbol on schematic so it matched other ground symbols
    * Changed TP1 to standard SparkFun test point footprint
2014-05-17 Completed testing on first v4.5 prototypes, and wrote up results in notes.txt. Also added some text to schematic including formula for calculating Max Current from Vref voltage.
2014-05-20 * Made TP1 bigger, and no longer covered with solder mask * Switched R5 to 2.4K Ohms to allow Vref down to 1V into driver * Set R17 to 6.8K to allow PFD input to select 'mixed-decay' mode * Swapped l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
2014-05-22 Based on SparkFun feedback * Replaced frame with newest version from SparkFun library * Replaced VCC symbol with newest version from SparkFun library * Move components so that keepout area around mou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
2014-05-23 Updating 2.4k to 2.49K resistor and updating to CC-SA 3.0
2014-08-13 added regular fiducials
2014-08-13 created giant panel v45
2015-03-03 Added BOM, updated for version 4.5
2015-03-03 Fixed 3 mistakes in the BOM: * R17 should be included in the build * R16 had wrong part number * R5 was wrong value.
2015-03-24 Adding in demo sketches, fixing directory name
2015-03-24 Update README.md
    Fixing links for tutorial.
2015-03-24 Update README.md
    Fixing image links and product link.
2015-08-19 Minor edits to some of schematic guide text for clarity of function (SJ1 mainly). Created schematic PDF so we can link to it in GitHub.
2019-06-19 Update SparkFun_Easy_Driver_Basic_Demo.ino
    Updating code to reflect 1000 steps based on description and how programmers start counting from 0 based on the `if()` statement's logic.
2020-02-22 Add gitpod config
    this commit adds support for Gitpod.io, a free automated
    dev environment that makes contributing and generally working on GitHub
    projects much easier. It allows anyone to start a ready-to-code dev
    environment for any branch, issue and pull request with a single click.
2020-10-29 Make sure step resolution is reset after calling SmallStepMode
    When calling SmallStepMode(), the MS1 and MS2 bits are flipped to move the motor to 1/8th step but are not reset after that which means any further call will remain in that mode without any way to ch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
    Resetting the two bits after the call to SmallStepMode to make sure the commands behave as expected.
